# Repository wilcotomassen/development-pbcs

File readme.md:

# Development PCBs

Collection of PCB's that make electronic development
a bit easier, such as breakout boards, minimal development
boards, programmers, etc.

# Breadboard packages (IC to board)

To find a matching breakout board for your IC or module, 
reference the following table

| IC or module               | Breakout board        |
|----------------------------|-----------------------|
| IC in SOIC-16 package      | [so16](/so16)         |
| IC in SOP-16 package       | [so16](/so16)         |
| IC in SO-16 package        | [so16](/so16)         |
| IC in MSOP-16 package      | [so16](/so16)         |
| IC in TSSOP-16 package     | [so16](/so16)         |

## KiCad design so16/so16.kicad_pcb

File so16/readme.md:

# Breakout board for SOIC/SOP/SO/MSOP/TSSOP 16pins

This dual sided breakout board allows to breadboard a
single IC. On one side it supports an IC of the package 
type:

* SOIC-16 or
* SOP-16 or
* SO-16

and on the other side one of package type:

* MSOP-16 or
* TSSOP-16

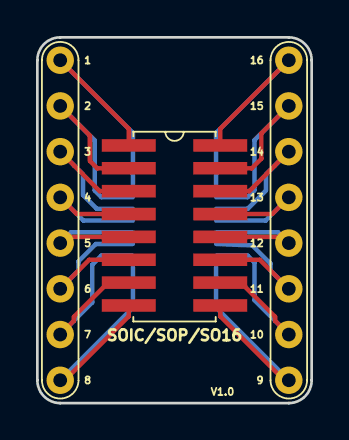
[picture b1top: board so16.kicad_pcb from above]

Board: 2 copper layers, 15.2 x 20.3 mm, 3 parts (1 on the bottom side), 16 nets.

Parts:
J1: bb2x8; bb_2x8_ds
U1: SOIC/SOP/SO16; soic_sop_so-16
U2: MSOP/TSSOP-16; msop_tssop-16

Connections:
unnamed: J1.1, U1.1, U2.16
unnamed: J1.2, U1.2, U2.15
unnamed: J1.3, U1.3, U2.14
unnamed: J1.4, U1.4, U2.13
unnamed: J1.5, U1.5, U2.12
unnamed: J1.6, U1.6, U2.11
unnamed: J1.7, U1.7, U2.10
unnamed: J1.8, U1.8, U2.9
unnamed: J1.9, U1.9, U2.8
unnamed: J1.10, U1.10, U2.7
unnamed: J1.11, U1.11, U2.6
unnamed: J1.12, U1.12, U2.5
unnamed: J1.13, U1.13, U2.4
unnamed: J1.14, U1.14, U2.3
unnamed: J1.15, U1.15, U2.2
unnamed: J1.16, U1.16, U2.1

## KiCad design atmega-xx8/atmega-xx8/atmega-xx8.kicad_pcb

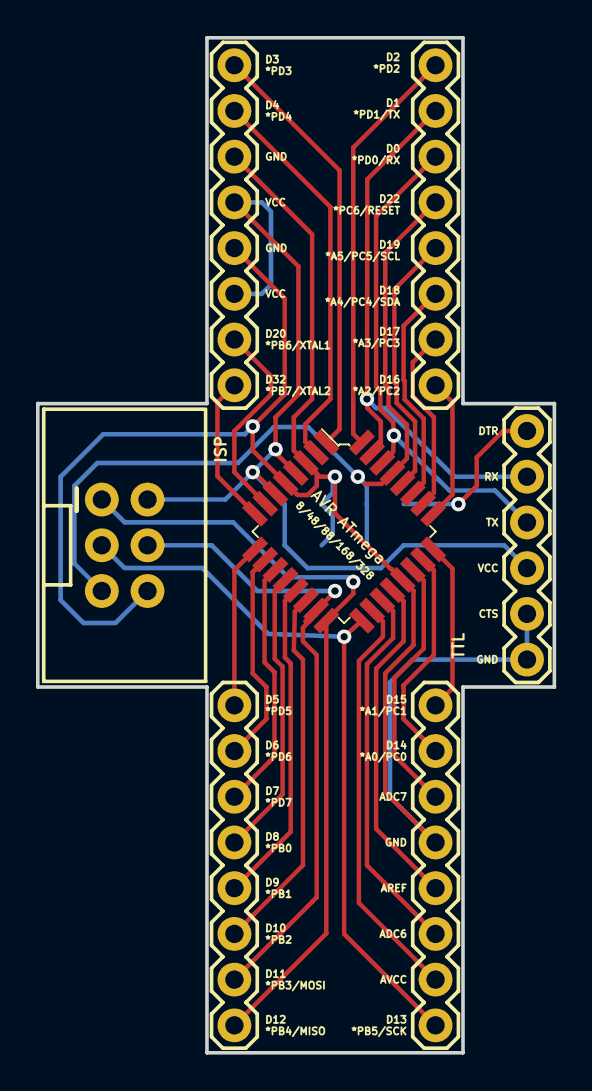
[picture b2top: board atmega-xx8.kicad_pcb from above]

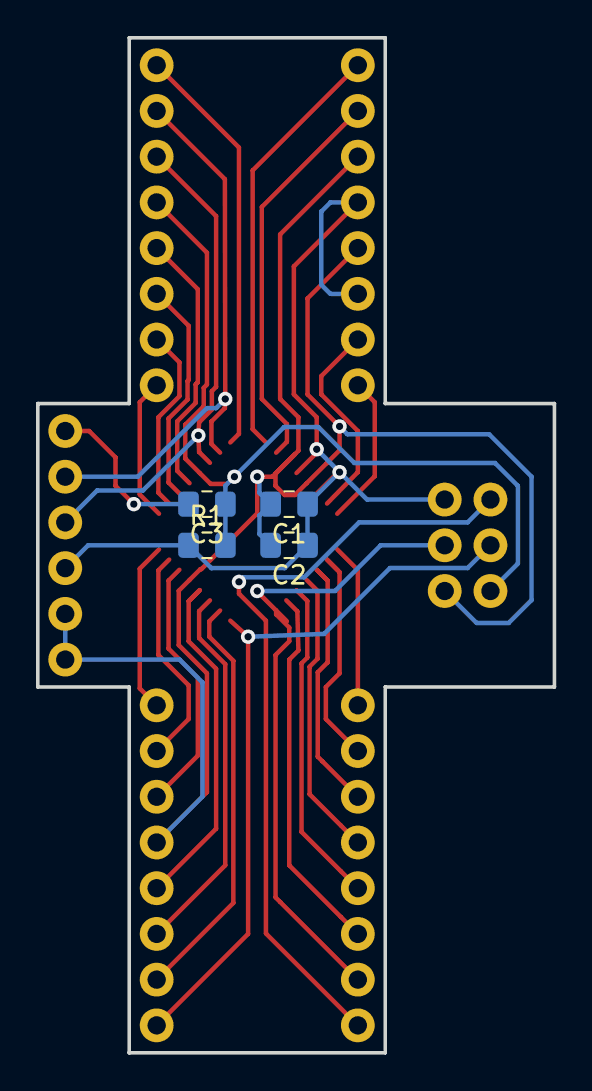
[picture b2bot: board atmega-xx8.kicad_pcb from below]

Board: 2 copper layers, 28.7 x 56.4 mm, 11 parts (4 on the bottom side), 30 nets.

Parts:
C1, C3: 100n; C_0805_2012Metric_Pad1.15x1.40mm_HandSolder
C2: 100n2; C_0805_2012Metric_Pad1.15x1.40mm_HandSolder
ISP: AVR-ISP-6; 2X3-SHROUDED
J1A1, J1B1, J2A1, J2B1: Conn_01x08_Male; 1X08
R1: 10K; R_0805_2012Metric_Pad1.15x1.40mm_HandSolder
TTL: 6_PIN_SERIAL_CABLEPTH; FTDI_BASIC
U1: ATMEGA8/48/88/168/328; TQFP-32_7x7mm

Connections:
ADC6: J2A1.3, U1.19
ADC_7: J2A1.6, U1.22
AREF: J2A1.4, U1.20
AVCC: J2A1.2, U1.18
D0_PD0_RX: J2B1.6, TTL.TXO, U1.30
D1_PD1_TX: J2B1.7, TTL.RXI, U1.31
D2_PD2: J2B1.8, U1.32
D3_PD3: J1A1.1, U1.1
D4_PD4: J1A1.2, U1.2
D5_PD5: J1B1.1, U1.9
D6_PD6: J1B1.2, U1.10
D7_PD7: J1B1.3, U1.11
D8_PB0: J1B1.4, U1.12
D9_PB1: J1B1.5, U1.13
D10_PB2: J1B1.6, U1.14
D11_PB3_MOSI: ISP.4, J1B1.7, U1.15
D12_PB4_MISO: ISP.1, J1B1.8, U1.16
D13_PB5_SCK: ISP.3, J2A1.1, U1.17
D14_A0_PC0: J2A1.7, U1.23
D15_A1_PC1: J2A1.8, U1.24
D16_A2_PC2: J2B1.1, U1.25
D17_A3_PC3: J2B1.2, U1.26
D18_A4_PC4_SDA: J2B1.3, U1.27
D19_A5_PC5_SCL: J2B1.4, U1.28
D20_PB6_XTAL1: J1A1.7, U1.7
D22_PC6_RESET: C3.1, ISP.5, J2B1.5, R1.2, U1.29
D32_PB7_XTAL2: J1A1.8, U1.8
GND_21: C1.2, C2.2, ISP.6, J1A1.3, J1A1.5, J2A1.5, TTL.CTS, TTL.GND, U1.3, U1.5, U1.21
unnamed: C3.2, TTL.DTR
VCC_4: C1.1, C2.1, ISP.2, J1A1.4, J1A1.6, R1.1, TTL.VCC, U1.4, U1.6

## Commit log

2018-10-14 Added gitignore
2018-10-14 Initial setup for atmega-xx8
2018-10-14 Soic-8 initial commit
2018-10-14 Added library
2018-10-14 Updated soic-8 with lib
2018-10-14 Implemented library footprints on soic-8
2018-10-14 Added soic-16 footprint
2018-10-14 Added U2x8 and BB2x8 to lib
2018-10-14 Added lib table
2018-10-15 Added soic-16, update library to add orientation to all soic footprints
2018-10-15 Added 3d to soic8 and soid16 footprint
2018-10-15 Added 2x7 symbol
2018-10-15 Added 2x7 breadboard footprint
2018-10-15 Added soic14 footprint
2018-10-15 Added soic-14
2018-10-21 Updated SOIC_SOP-SO footprints, added MSOP-TSSOP footprints
2018-10-22 Updated 2x6 footprints, added so16 breakout
2018-10-22 Added readme
2018-10-22 Updated readme (alignment in table)
2018-10-22 Added render
2019-04-11 SOIC14
